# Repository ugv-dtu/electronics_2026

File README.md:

## Project Structure

```
Embedded_UGVC/
│
├── assets/
│   ├── PCB Files/         # KiCad Files
│   ├── Datasheet/         # IC, MCU and other datasheets we need
│
├──platformio.ini
├──src/               # Source files (.cpp)
├──include/           # Header files (.h)
├──lib/               # Private/project-specific libraries
├──test/              # Unit tests
│
└── README.md
```

---

## `src/` — Source Files

One `.cpp` file per subsystem. **Do not put everything in `main.cpp`.**

- `main.cpp` — Only `setup()` and `loop()`. Calls functions from other modules.
- Add a new `.cpp` for every new subsystem (e.g. `motor_control.cpp`, `encoder.cpp`, `jetson_comm.cpp`, `pid.cpp`, `imu.cpp`).

---

## `include/` — Header Files

Every `.cpp` in `src/` gets a matching `.h` here. Use `#pragma once` at the top of every header.h

- **All pin numbers, baud rates, and tuning constants go in `config.h`** — never hardcode them inside `.cpp` files.

---

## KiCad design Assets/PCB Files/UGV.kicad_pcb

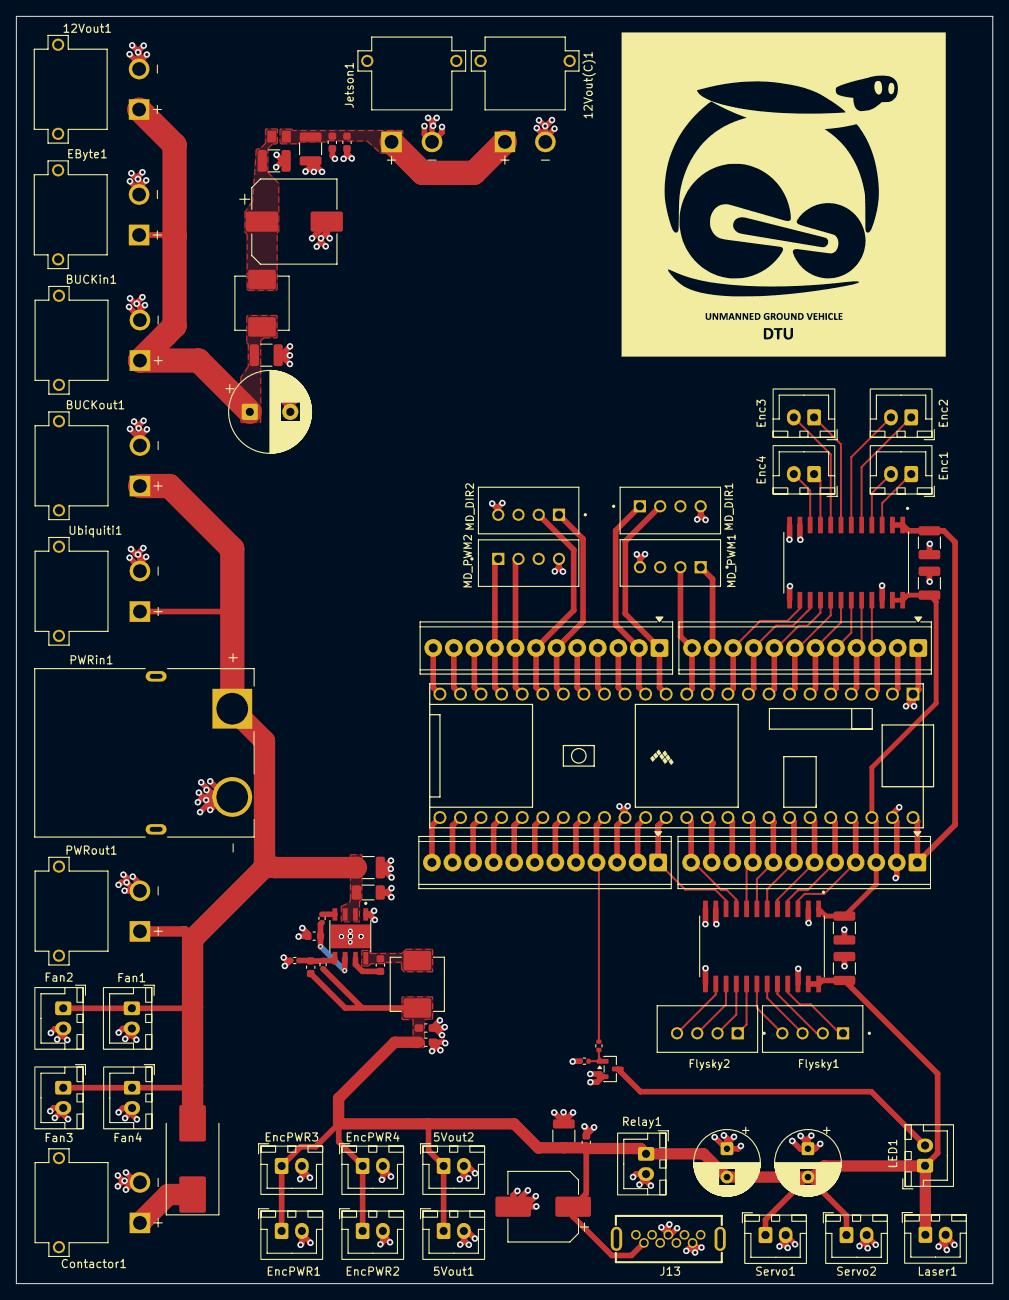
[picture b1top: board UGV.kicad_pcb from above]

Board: 2 copper layers, 120.6 x 156.5 mm, 77 parts (0 on the bottom side), 74 nets.

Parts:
5Vout1, 5Vout2: B2B-XH-A; JST_XH_B2B-XH-A_1x02_P2.50mm_Vertical
12Vout1, 12Vout(C)1: XT30PW-M; AMASS_XT30PW-M
BUCKin1: XT30PW-M; AMASS_XT30PW-M
BUCKout1: XT30PW-M; AMASS_XT30PW-M
C1, C3, C5, C8, C9, C15: 10uF; C_1210_3225Metric
C2: 100nF; C_0603_1608Metric
C4: 150uF; CP_Elec_8x10.5
C6, C10: 470uF; CP_Radial_D8.0mm_P3.50mm
C7, C12: 22uF; C_1210_3225Metric
C16: 1uF; C_0603_1608Metric
C17: 0.1uF; C_0603_1608Metric
Cboot1: 0.1uF; C_0603_1608Metric
Cff1: 22pF; C_0603_1608Metric
Chf1: 220nF; C_1206_3216Metric
Cin1: 10uF; C_1210_3225Metric
Contactor1: XT30PW-M; AMASS_XT30PW-M
Cout1, Cout2: 22uF; C_0603_1608Metric_Pad1.08x0.95mm_HandSolder
Cp1: 330uF; CP_Radial_D10.0mm_P5.00mm
Cp3: 220uF; CP_Elec_10x10
Cvcc1: 1uF; C_0603_1608Metric
D1: D_Schottky; D_SMC_Handsoldering
EByte1: XT30PW-M; AMASS_XT30PW-M
Enc1, Enc2, Enc3, Enc4: B2B-XH-A; JST_XH_B2B-XH-A_1x02_P2.50mm_Vertical
EncPWR1, EncPWR2, EncPWR3, EncPWR4: B2B-XH-A; JST_XH_B2B-XH-A_1x02_P2.50mm_Vertical
FB1: 1k@1k; BEADC2012X105N
Fan1, Fan2, Fan3, Fan4: B2B-XH-A; JST_XH_B2B-XH-A_1x02_P2.50mm_Vertical
Flysky1, Flysky2: B4B-XH-A_LF__SN_; JST_B4B-XH-A_LF__SN_
J13: USB3_A; USB-3.0-TH_U233-091N-4BLPC17-11
J15, J16, J17, J18: Screw_Terminal_01x12; TerminalBlock_Phoenix_MPT-0,5-12-2.54_1x12_P2.54mm_Horizont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
Jetson1: XT30PW-M; AMASS_XT30PW-M
L1: 2.2uH; L_Vishay_IHLP-2525
L2: 10uH; L_Vishay_IHLP-2525
LED1: B2B-XH-A; JST_XH_B2B-XH-A_1x02_P2.50mm_Vertical
Laser1: B2B-XH-A; JST_XH_B2B-XH-A_1x02_P2.50mm_Vertical
MD_DIR1, MD_DIR2: B4B-XH-A_LF__SN_; JST_B4B-XH-A_LF__SN_
MD_PWM1, MD_PWM2: B4B-XH-A_LF__SN_; JST_B4B-XH-A_LF__SN_
PWRin1: XT90PW-M; AMASS_XT90PW-M
PWRout1: XT30PW-M; AMASS_XT30PW-M
Q1: AO3400A; SOT-23
R1: 100k; R_0402_1005Metric
R2: 100; R_0402_1005Metric
R3: 10k; R_0402_1005Metric
Relay1: B2B-XH-A; JST_XH_B2B-XH-A_1x02_P2.50mm_Vertical
Rfbb1: 24.9k; R_0402_1005Metric
Rfbt1: 100k; R_0402_1005Metric
Servo1, Servo2: B2B-XH-A; JST_XH_B2B-XH-A_1x02_P2.50mm_Vertical
U2: LMR33630ADDA; VREG_LM5017MR_NOPB
U3, U5: SN74LVC8T245; SOIC127P1030X265-24N
U4: Teensy4.1; Teensy41
Ubiquiti1: XT30PW-M; AMASS_XT30PW-M

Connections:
/0: J17.2, U4.2 (0_RX1_CRX2_CS1)
/1: J17.3, U3.21 (B1), U4.3 (1_TX1_CTX2_MISO1)
/2: J17.4, U3.20 (B2), U4.4 (2_OUT2)
/3: J17.5, U3.19 (B3), U4.5 (3_LRCLK2)
/3V3: C5.2, C8.2, J15.3, J18.3, U3.23 (V_{CCB}), U3.24 (V_{CCB}), U4.15 (3V3), U4.46 (3V3), U5.1 (V_{CCA})
/4: J17.6, U3.18 (B4), U4.6 (4_BCLK2)
/5: J17.7, U3.17 (B5), U4.7 (5_IN2)
/6: J17.8, U3.16 (B6), U4.8 (6_OUT1D)
/7: J17.9, U3.15 (B7), U4.9 (7_RX2_OUT1A)
/8: J17.10, U3.14 (B8), U4.10 (8_TX2_IN1)
/9: J17.11, MD_PWM1.1, U4.11 (9_OUT1C)
/10: J17.12, MD_PWM1.2, U4.12 (10_CS_MQSR)
/11: J18.1, MD_DIR1.2, U4.13 (11_MOSI_CTX1)
/12: J18.2, MD_DIR1.1, U4.14 (12_MISO_MQSL)
/13: J16.2, U4.35 (13_SCK_LED)
/14: J16.1, U4.36 (14_A0_TX3_SPDIF_OUT), U5.10 (A8)
/15: J15.12, U4.37 (15_A1_RX3_SPDIF_IN), U5.9 (A7)
/16: J15.11, U4.38 (16_A2_RX4_SCL1)
/17: J15.10, U4.39 (17_A3_TX4_SDA1)
/18: J15.9, U4.40 (18_A4_SDA), U5.8 (A6)
/19: J15.8, U4.41 (19_A5_SCL), U5.7 (A5)
/20: J15.7, U4.42 (20_A6_TX5_LRCLK1), U5.6 (A4)
/21: J15.6, U4.43 (21_A7_RX5_BCLK1), U5.5 (A3)
/22: J15.5, U4.44 (22_A8_CTX1), U5.4 (A2)
/23: J15.4, U4.45 (23_A9_CRX1_MCLK1), U5.3 (A1)
/24: J18.4, U4.16 (24_A10_TX6_SCL2)
/25: J18.5, U4.17 (25_A11_RX6_SDA2)
/26: J18.6, MD_DIR2.1, U4.18 (26_A12_MOSI1)
/27: J18.7, MD_DIR2.2, U4.19 (27_A13_SCK1)
/28: J18.8, MD_PWM2.2, U4.20 (28_RX7)
/29: J18.9, MD_PWM2.1, U4.21 (29_TX7)
/30: J18.10, U4.22 (30_CRX3)
/31: J18.11, U4.23 (31_CTX3)
/32: J18.12, U4.24 (32_OUT1B)
/33: J16.12, U4.25 (33_MCLK2)
/34: J16.11, U4.26 (34_RX8)
/35: J16.10, U4.27 (35_TX8)
/36: J16.9, U4.28 (36_CS)
/37: J16.8, U4.29 (37_CS)
/38: J16.7, U4.30 (38_CS1_IN1)
/39: J16.6, U4.31 (39_MISO1_OUT1A)
/40: J16.5, U4.32 (40_A16)
/41: J16.4, R2.2, U4.33 (41_A17)
/Vin: C3.2, J15.1, U3.1 (V_{CCA}), U3.2 (DIR), U4.48 (VIN)
/Vout: 5Vout1.1, 5Vout2.1, C1.2, C2.1, C4.1, C6.2, C9.2, C10.2, Cff1.1, Cout1.1, Cout2.1, EncPWR1.1, EncPWR2.1, EncPWR3.1, EncPWR4.1, J13.1 (VBUS), L2.2, LED1.1, Laser1.1, Relay1.1, Rfbt1.1, Servo1.1, Servo2.1, U5.23 (V_{CCB}), U5.24 (V_{CCB})
GND: 5Vout1.2, 5Vout2.2, 12Vout1.N, 12Vout(C)1.N, BUCKin1.N, BUCKout1.N, C1.1, C2.2, C3.1, C4.2, C5.1, C6.1, C7.2, C8.1, C9.1, C10.1, C12.2, C15.2, C16.2, C17.2, Chf1.2, Cin1.2, Contactor1.N, Cout1.2, Cout2.2, Cp1.2, Cp3.2, Cvcc1.2, EByte1.N, EncPWR1.2, EncPWR2.2, EncPWR3.2, EncPWR4.2, Fan1.2, Fan2.2, Fan3.2, Fan4.2, J13.4 (GND), J13.7 (DRAIN), J15.2, J16.3, J17.1, Jetson1.N, Laser1.2, MD_DIR1.4, MD_DIR2.4, MD_PWM1.4, MD_PWM2.4, PWRin1.N, PWRout1.N, Q1.2 (S), R3.1, Relay1.2, Rfbb1.2, Servo1.2, Servo2.2, U2.1 (GND), U2.9 (GND), U3.11 (GND), U3.12 (GND), U3.13 (GND), U3.22 (~OE), U4.1 (GND), U4.34 (GND), U4.47 (GND), U5.2 (DIR), U5.11 (GND), U5.12 (GND), U5.13 (GND), U5.22 (~OE), Ubiquiti1.N
unnamed: 12Vout1.P, BUCKin1.P, C7.1, Cp1.1, EByte1.P, L1.1
unnamed: 12Vout(C)1.P, C15.1, C16.1, C17.1, FB1.2, Jetson1.P
unnamed: C12.1, Cp3.1, FB1.1, L1.2
unnamed: BUCKout1.P, Chf1.1, Cin1.1, D1.2 (A), Fan1.1, Fan2.1, Fan3.1, Fan4.1, PWRin1.P, PWRout1.P, U2.2 (VIN), U2.3 (EN), Ubiquiti1.P
unnamed: Contactor1.P, D1.1 (K)
unnamed: LED1.2, Q1.3 (D)
unnamed: Q1.1 (G), R2.1, R3.2
unnamed: Cboot1.1, U2.7 (BOOT)
unnamed: Cff1.2, Rfbb1.1, Rfbt1.2, U2.5 (FB)
unnamed: R1.2, U2.4 (PG)
unnamed: Cboot1.2, L2.1, U2.8 (SW)
unnamed: Cvcc1.1, R1.1, U2.6 (VCC)
unnamed: Enc1.1, U3.3 (A1)
unnamed: Enc1.2, U3.4 (A2)
unnamed: Enc2.1, U3.5 (A3)
unnamed: Enc2.2, U3.6 (A4)
unnamed: Enc3.1, U3.7 (A5)
unnamed: Enc3.2, U3.8 (A6)
unnamed: Enc4.1, U3.9 (A7)
unnamed: Enc4.2, U3.10 (A8)
unnamed: Flysky1.1, U5.21 (B1)
unnamed: Flysky1.2, U5.20 (B2)
unnamed: Flysky1.3, U5.19 (B3)
unnamed: Flysky1.4, U5.18 (B4)
unnamed: Flysky2.1, U5.17 (B5)
unnamed: Flysky2.2, U5.16 (B6)
unnamed: Flysky2.3, U5.15 (B7)
unnamed: Flysky2.4, U5.14 (B8)

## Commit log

2026-04-04 Changed Capacitor in LC Filtering
2026-04-14 files removed
2026-04-24 Added Custom Model and Updated PCB
2026-04-25 Added Logo and edited layout
2026-05-22 Routing changes in the LMR IC and a few small changes too
